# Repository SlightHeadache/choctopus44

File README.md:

# Choctopus44

*Current version: 2.0*

Choctopus44 is low profile, Choc spaced, optionally hotswappaple 44-key column staggered keyboard with a rotary encoder.
It is loosely based on **[gtips's REVIUNG project](https://github.com/gtips/reviung)**, specifically REVIUNG41, but has deviated from it significantly during its development.

## Known issues with v2

While all the main issues of the original Choctopus44 prototypes were addressed during the development of v2, some new minor arose during it's development.

  * Switch plate does not accommodate all encoders properly. Certain non-Alps THD encoders, and SMD encoders may require filing the plate's encoder cut out to be a little bigger.
    See **[encoder documentation](documents/encoder.md)**.
  * Flaky Bluetooth behaviour in certain edge cases while using Nice!Nano, seems like certain devices don't like Nice!Nano's/ZMK's Bluetooth handling
  * During fabrication with tented vias the battery circuit vias can easily remain exposed, at least with JLCPCB. By my understanding this is caused by the solder mask liquid seeping
    into the via's hole. This doesn't seem to affect other vias as only the battery vias are slightly larger than usual. This should be avoidable by using plugged vias instead, but as
    that increases the cost of manufacturing I'm going to create a hotfix version in the future that shrinks those vias to the standard size to alleviate the issue.

## TODO

  * Add documentation for v2's plate and bottom foams

## Parts list

### Main components

| Part                                          | Count   | Optional | Notes |
| --------------------------------------------- |:-------:|:--------:|:-----:|
| PCB                                           | 1       |          |       |
| Diode [1N4148 SMD or THD]                     | 45      |          |       |
| Kailh Choc sockets                            | 44      | x        |       |
| Tactile switch TL3342 or compatible           | 1       |          | Stem height of 1.54mm used in tested builds |
| Slide switch PCM12 or compatible              | 1       | x        | Only useful if a wireless microcontroller is used in conjunction with a battery |
| EC11 encoder or compatible                    | 1       | x        | See detailed **[encoder documentation](documents/encoder.md)**; Can also be replaced with a Choc or an MX switch |
| ProMicro/Nice!Nano or compatible              | 1       |          |       |
| MCU socket (or header rows)                   | 1 (2)   | x        |       |
| Kailh Choc key switch                         | 44 (45) |          |       |
| 3.7 Volt battery                              | 1       | x        | Only useful if a wireless microcontroller is used |
| 100 nF capacitors (axial or 1206 SMD)         | 2       | x        | Used in the optional encoder filter circuit |
| 10 kOhm resistors (axial or 1206 SMD)         | 4       | x        | ***Not adviced!*** Can be used in the encoder filter circuit, but can cause issues at least with Nice!Nanos |

### Case hardware

| Part                                          | Count   | Optional | Notes |
| --------------------------------------------- |:-------:|:--------:|:-----:|
| Top plate [PCB]                               | 1       |          |       |
| Bottom plate [PCB]                            | 1       |          |       |
| M2 stand off 5mm                              | 9       |          |       |
| M2 screw 3mm                                  | 15 (18) |          | 18 needed if MCU cover is not used |
| Rubber bump ons                               | ~11     |          | Depending on your bump ons you might need to use more, or get away with using fewer |

### Example extra case hardware if using MCU cover

**Note:** The length of the required MCU cover stand-offs is highly dependant on the used battery and its orientation (assuming one is used at all), and the used MCU socket.
With the listed screws and stand offs, a 5mm thick battery can fit between the MCU and the MCU cover without much issue as long as the the MCU socket is slim enough.

| Part                                          | Count | Optional | Notes |
| --------------------------------------------- |:-----:|:--------:|:-----:|
| M2 stand off 10mm                             | 3     |          |       |
| M2 screw 10mm                                 | 3     |          | Used for the bottom plate stand offs; 3mm screws used on the MCU cover |

### Misc hardware

| Part                                          | Count   | Optional | Notes |
| --------------------------------------------- |:-------:|:--------:|:-----:|
| Choc spacing compatible keycaps (e.g. MBK)    | 44 (45) |          |       |

## Firmware

***Please note!*** Should you utilize a pre-existing QMK/Vial/ZMK set up, you may need to do additional steps not defined here before you can succesfully build the firmware.
Whether or not that's required is highly dependant on the version and the state of your pre-existing set up!

*Pre-built binaries TBA*

 * QMK: https://github.com/SlightHeadache/qmk_firmware : branch `choctopus_project`
   * If you want to utilize your existing QMK set up, navigate to it and run the following `bash` command to fetch and switch to the WIP branch.
     If you are using git via PowerShell or Windows CMD, remember to switch the `&&`s to semicolons. 
     Remember to switch to your preferred local branch if you wish to meddle with other keyboards.
     ```sh
     git remote add choctopus_project git@github.com:SlightHeadache/qmk_firmware.git && git fetch choctopus_project && git checkout --track -b choctopus_project choctopus_project/choctopus_project
     ```
 * Vial: https://github.com/SlightHeadache/vial-qmk : branch `choctopus44-vial`
   * If you want to utilize your existing Vial set up, navigate to it and run the following `bash` command to fetch and switch to the WIP branch.
     If you are using git via PowerShell or Windows CMD, remember to switch the `&&`s to semicolons. 
     Remember to switch to your preferred local branch if you wish to meddle with other keyboards.
     ```sh
     git remote add choctopus44-vial git@github.com:SlightHeadache/vial-qmk.git && git fetch choctopus44-vial && git checkout --track -b choctopus44-vial choctopus44-vial/choctopus44-vial
     ```
 * ZMK: https://github.com/SlightHeadache/zmk : branch `choctopus44`
   * For an easy online build using GitHub actions, fork https://github.com/SlightHeadache/zmk-config and enable Actions from *Settings -> Actions -> Allow all actions*. Then clone your fork.
     The keymap file can be found from path `config/boards/shields/choctopus44/choctopus44.keymap` in the cloned repo. The firmware should now build automagically when you push your keymap changes to GitHub.
     The built firmware can be found from under the GitHub Actions run's summary (e.g. https://github.com/SlightHeadache/zmk-config/actions/runs/6002979887), *not* under either of the build steps.
   * If you want to utilize your existing ZMK set up, navigate to it and run the following `bash` command to fetch and switch to the WIP branch.
     If you are using git via PowerShell or Windows CMD, remember to switch the `&&`s to semicolons. 
     Remember to switch to your preferred local branch if you wish to meddle with other keyboards.
     ```sh
     git remote add choctopus44 git@github.com:SlightHeadache/zmk.git && git fetch choctopus44 && git checkout --track -b choctopus44 choctopus44/choctopus44
     ```

## Build guide

See [build guide](documents/buildguide.md).

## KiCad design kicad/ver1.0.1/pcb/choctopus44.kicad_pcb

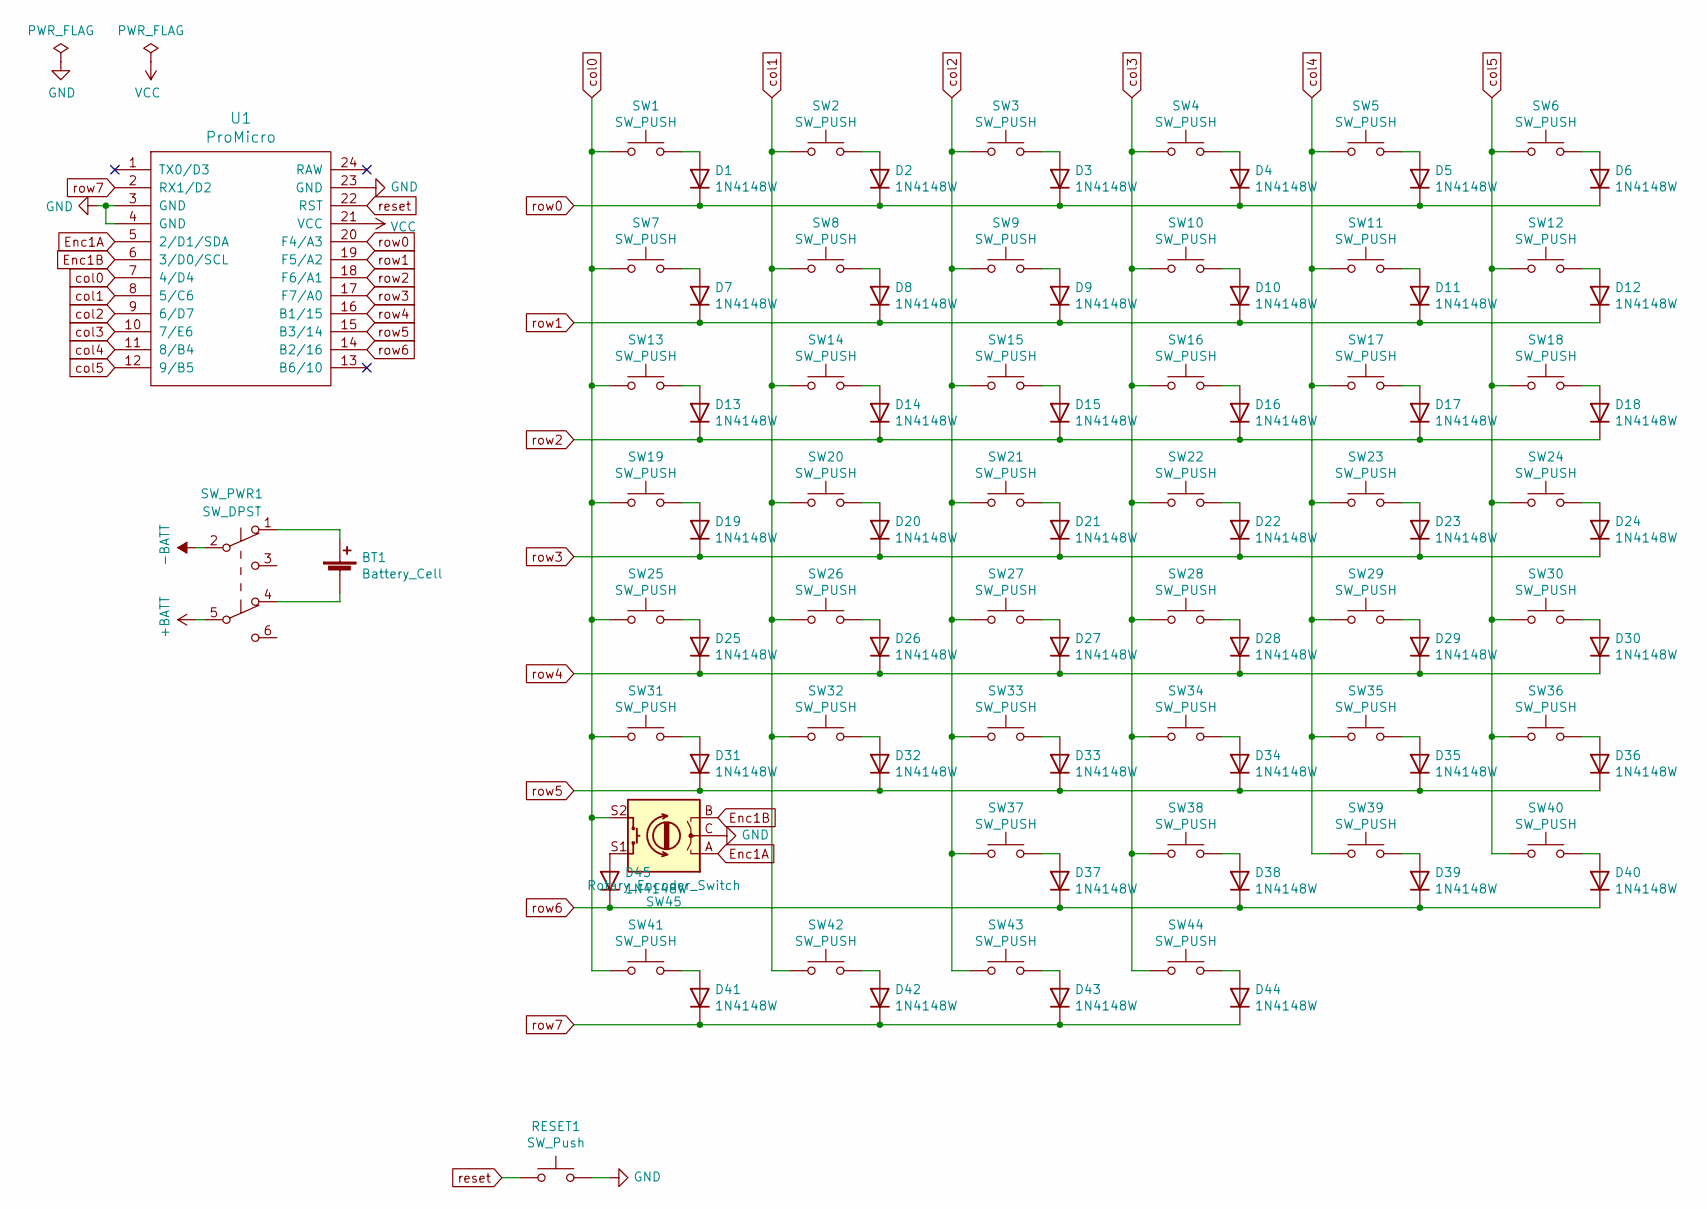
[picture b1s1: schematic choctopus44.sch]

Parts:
BT1: Battery_Cell; PinHeader_1x02_P2.00mm_Vertical
D1, D2, D3, D4, D5, D6, D7, D8, D9, D10, D11, D12, D13, D14, D15, D16, D17, D18, D19, D20, D21, D22, D23, D24, D25, D26, D27, D28, D29, D30, D31, D32, D33, D34, D35, D36, D37, D38, D39, D40, D41, D42, D43, D44, D45: 1N4148W; Diode-dual
RESET1: SW_Push; SW_PUSH_6mm
SW1, SW2, SW3, SW4, SW5, SW6, SW7, SW8, SW9, SW10, SW11, SW12, SW13, SW14, SW15, SW16, SW17, SW18, SW19, SW20, SW21, SW22, SW23, SW24, SW25, SW26, SW27, SW28, SW29, SW30, SW31, SW32, SW33, SW34, SW35, SW36, SW37, SW38, SW39, SW40, SW41, SW42, SW43, SW44: SW_PUSH; Kailh_socket_PG1350_optional
SW45: Rotary_Encoder_Switch; RotaryEncoder_Alps_EC11E-Switch_Vertical_H20mm-SMD-support
SW_PWR1: SW_DPST; SW_E-Switch_EG1271_DPDT
U1: ProMicro; ArduinoProMicro

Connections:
+BATT: SW_PWR1.5 (B); also elsewhere on the board
-BATT: SW_PWR1.2 (B); also elsewhere on the board
Enc1A: SW45.A, U1.5 (2/D1/SDA)
Enc1B: SW45.B, U1.6 (3/D0/SCL)
GND: RESET1.2, SW45.C, U1.3 (GND), U1.4 (GND), U1.23 (GND)
unnamed: BT1.1 (+), SW_PWR1.1 (A)
unnamed: BT1.2 (-), SW_PWR1.4 (A)
unnamed: D1.2 (A), SW1.2
unnamed: D2.2 (A), SW2.2
unnamed: D3.2 (A), SW3.2
unnamed: D4.2 (A), SW4.2
unnamed: D5.2 (A), SW5.2
unnamed: D6.2 (A), SW6.2
unnamed: D7.2 (A), SW7.2
unnamed: D8.2 (A), SW8.2
unnamed: D9.2 (A), SW9.2
unnamed: D10.2 (A), SW10.2
unnamed: D11.2 (A), SW11.2
unnamed: D12.2 (A), SW12.2
unnamed: D13.2 (A), SW13.2
unnamed: D14.2 (A), SW14.2
unnamed: D15.2 (A), SW15.2
unnamed: D16.2 (A), SW16.2
unnamed: D17.2 (A), SW17.2
unnamed: D18.2 (A), SW18.2
unnamed: D19.2 (A), SW19.2
unnamed: D20.2 (A), SW20.2
unnamed: D21.2 (A), SW21.2
unnamed: D22.2 (A), SW22.2
unnamed: D23.2 (A), SW23.2
unnamed: D24.2 (A), SW24.2
unnamed: D25.2 (A), SW25.2
unnamed: D26.2 (A), SW26.2
unnamed: D27.2 (A), SW27.2
unnamed: D28.2 (A), SW28.2
unnamed: D29.2 (A), SW29.2
unnamed: D30.2 (A), SW30.2
unnamed: D31.2 (A), SW31.2
unnamed: D32.2 (A), SW32.2
unnamed: D33.2 (A), SW33.2
unnamed: D34.2 (A), SW34.2
unnamed: D35.2 (A), SW35.2
unnamed: D36.2 (A), SW36.2
unnamed: D37.2 (A), SW37.2
unnamed: D38.2 (A), SW38.2
unnamed: D39.2 (A), SW39.2
unnamed: D40.2 (A), SW40.2
unnamed: D41.2 (A), SW41.2
unnamed: D42.2 (A), SW42.2
unnamed: D43.2 (A), SW43.2
unnamed: D44.2 (A), SW44.2
unnamed: D45.2 (A), SW45.S1
VCC: U1.21 (VCC)
col0: SW1.1, SW7.1, SW13.1, SW19.1, SW25.1, SW31.1, SW41.1, SW45.S2, U1.7 (4/D4)
col1: SW2.1, SW8.1, SW14.1, SW20.1, SW26.1, SW32.1, SW42.1, U1.8 (5/C6)
col2: SW3.1, SW9.1, SW15.1, SW21.1, SW27.1, SW33.1, SW37.1, SW43.1, U1.9 (6/D7)
col3: SW4.1, SW10.1, SW16.1, SW22.1, SW28.1, SW34.1, SW38.1, SW44.1, U1.10 (7/E6)
col4: SW5.1, SW11.1, SW17.1, SW23.1, SW29.1, SW35.1, SW39.1, U1.11 (8/B4)
col5: SW6.1, SW12.1, SW18.1, SW24.1, SW30.1, SW36.1, SW40.1, U1.12 (9/B5)
reset: RESET1.1, U1.22 (RST)
row0: D1.1 (K), D2.1 (K), D3.1 (K), D4.1 (K), D5.1 (K), D6.1 (K), U1.20 (F4/A3)
row1: D7.1 (K), D8.1 (K), D9.1 (K), D10.1 (K), D11.1 (K), D12.1 (K), U1.19 (F5/A2)
row2: D13.1 (K), D14.1 (K), D15.1 (K), D16.1 (K), D17.1 (K), D18.1 (K), U1.18 (F6/A1)
row3: D19.1 (K), D20.1 (K), D21.1 (K), D22.1 (K), D23.1 (K), D24.1 (K), U1.17 (F7/A0)
row4: D25.1 (K), D26.1 (K), D27.1 (K), D28.1 (K), D29.1 (K), D30.1 (K), U1.16 (B1/15)
row5: D31.1 (K), D32.1 (K), D33.1 (K), D34.1 (K), D35.1 (K), D36.1 (K), U1.15 (B3/14)
row6: D37.1 (K), D38.1 (K), D39.1 (K), D40.1 (K), D45.1 (K), U1.14 (B2/16)
row7: D41.1 (K), D42.1 (K), D43.1 (K), D44.1 (K), U1.2 (RX1/D2)

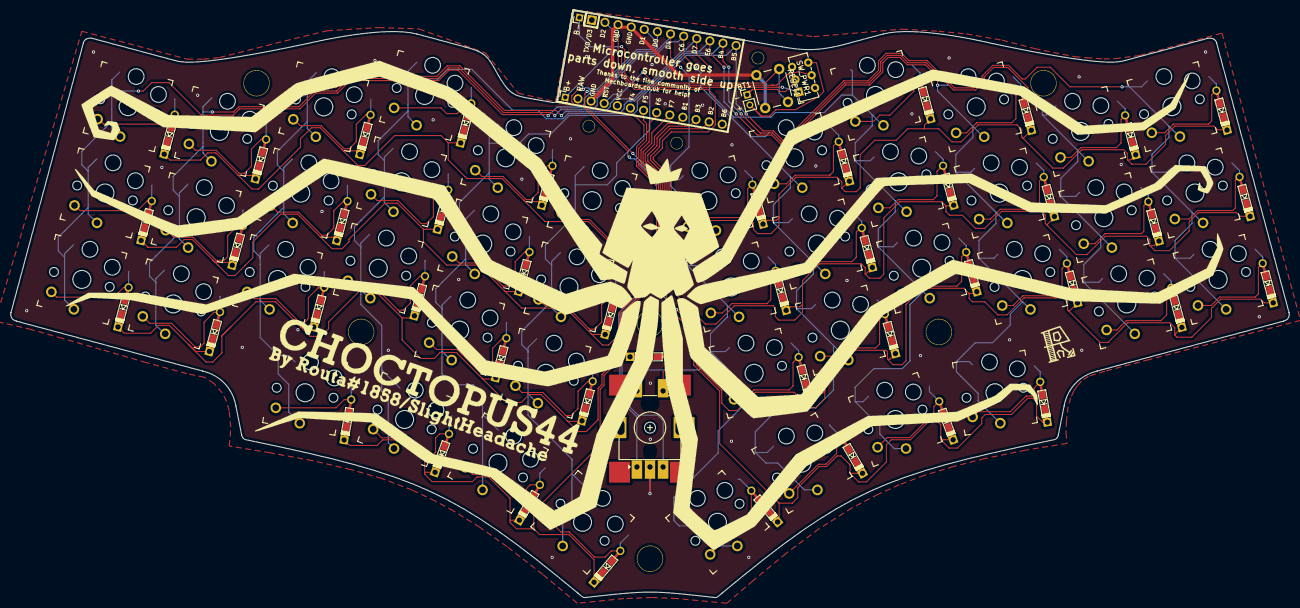
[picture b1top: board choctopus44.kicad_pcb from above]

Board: 2 copper layers, 243.9 x 111.9 mm, 105 parts (1 on the bottom side), 67 nets.

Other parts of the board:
B+: PinHeader_1x01_P2.00mm_Vertical
B-: PinHeader_1x01_P2.00mm_Vertical
H1: H1; HOLE
H6, H6#2: H6; HOLE
H8, H8#2: H8; HOLE
H11: H11; HOLE
H12: H12; HOLE_2.2mm
H13: H13; HOLE_2.2mm
H14: H14; HOLE_2.2mm

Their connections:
+BATT: B+.1; also elsewhere on the board
-BATT: B-.1; also elsewhere on the board

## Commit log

2021-08-09 Add image
2021-08-09 Fixed typos
2021-08-09 Fix spelling
2021-08-10 Change some wording
2021-08-23 Add more info
    * Add more issues to the "known issues list"
    * Add physical layout PDF
2021-08-29 Revise documentation
    * Add documentation about slide switch issues
    * Add documentation about USB plug collision issue
    * Add build guide
    * Fix wording issues
2021-09-13 Emphasized warning of issues in the current revision
2021-09-23 * Add mention of partial visual build guide by @ItsFiremanSam * Add guide for getting the QMK fork for Choctopus44
2021-09-23 * Update part list * Update introduction for clarity
2021-09-25 * Add guidance for ZMK firmware via GitHub action * Update link to ItsFiremanSam's build guide
2021-10-03 Revised README.md
2021-10-14 Sorted some Error
2021-10-14 forgot to commit schematic changes
2021-11-01 Initial restructuring for revision 1.0.1
    - Add link to new build guide
    - Might include some of the changes in Envious-Data's PR
2021-11-01 sorted schematic
2021-11-01 sorted PCB *and schematic some more*
2022-01-15 RC1, filtering circuit
2022-01-16 backups etc
2022-01-18 Schema done, PCB work restarted
2022-01-24 PCB work started for RC-1
2022-02-04 todo: adjust component positions and reroute everything
2022-02-04 components connected, but a lot of work is still needed
2022-02-04 clean up some ground planes and silk screen orientations
2022-06-06 Add missing LICENSE file
2022-07-12 revise ver1.0 RC-1 routing; remove redudant backups
2022-08-01 WIP: major layout reworks
2022-08-02 Change to Single Sided SMD diodes; continue trace rework
2022-10-18 initial error-free routing for RC-1
2022-12-11 rerouted some stuff, but more routing will probably be done
2023-01-06 routing more or less done
2023-01-06 fix routing clearances
2023-01-12 more routing
2023-01-21 more routing clean up
2023-01-29 save point before minor component position fixes
2023-03-13 fix tiny switch alignment issues
2023-03-13 revise power and reset circuits
2023-04-11 revise encoder area
2023-04-15 tweak diode locations
2023-04-27 update edge cuts
2023-04-28 tweak edges
2023-04-29 tweak silk screens
2023-05-01 tiny tweaks
2023-05-07 new silk screens
2023-05-08 hopefully final tweaks for the PCB
2023-05-08 ver1.0 RC -> ver2.0
2023-05-08 remove references to 3rd party 3d models due to unclear licensing
2023-05-08 change the 'chin' of the board just a bit
2023-05-11 initial switch plate files
2023-05-11 fix board outline, remove some silk screen texts
2023-05-14 silk screen changes
2023-05-15 new gerbers etc
2023-05-23 initial files for top foam/filler layer
2023-05-24 bottom fill layer
2023-05-26 add A4 lasering files for fillers, remove old files
2023-05-30 fix DXFs
2023-06-18 simplify filler foam files for faster laser cutting
2023-07-12 modify foam files to have better cutting tolerances
2023-07-17 further optimize switch plate foams for laser cutting
2023-08-03 WIP: new documentation
2023-08-12 update build guide
2023-08-15 update docs a bit
2023-08-19 added images to the new build guide
2023-08-20 add encoder compatibility graph
2023-08-20 small tweaks to documentation
2023-08-21 add a mention of gtips's REVIUNG
2023-08-21 fix typo
2023-08-21 clean up the repo a bit
2023-09-26 Update firmware section of Readme, add missing encoder filter parts to parts list
2023-09-26 tweak wording regarding firmwares
2023-10-02 tweak build guide a little bit
